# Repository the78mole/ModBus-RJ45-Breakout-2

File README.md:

# Modbus-RJ45-Breakout
A breakout board for Dual-ModBus-over-Twisted-Pair (RJ45) with isolated converters option

Here are some images of the first prototype, assembled with isolating RS485 transceivers. Echo already works, real testing on a ModBus will take place soon.

## Production Files

This repository includes an automated workflow that generates production-ready files for PCB manufacturing and assembly. The workflow creates:

- **Gerber Files** - Ready for PCB manufacturer submission
- **Drill Files** - For via and hole drilling
- **Schematic PDF** - Complete circuit documentation
- **Interactive BOM** - HTML component placement guide
- **3D STEP Model** - For mechanical design verification
- **PCB Renders** - Professional visualizations and assembly drawings

### Using the Production Workflow

The workflow automatically runs on:
- Every push to `main` branch
- Every pull request
- Manual trigger via "Actions" tab

**For Pull Requests:** Download artifacts directly from the workflow run to review changes.

**For Releases:** Production files are automatically attached to GitHub releases with semantic versioning.

### Manual Generation

To generate production files locally, ensure you have the required tools installed and run:

```bash
.github/scripts/generate-production-files.sh
```

Files will be generated in the `production/` directory.

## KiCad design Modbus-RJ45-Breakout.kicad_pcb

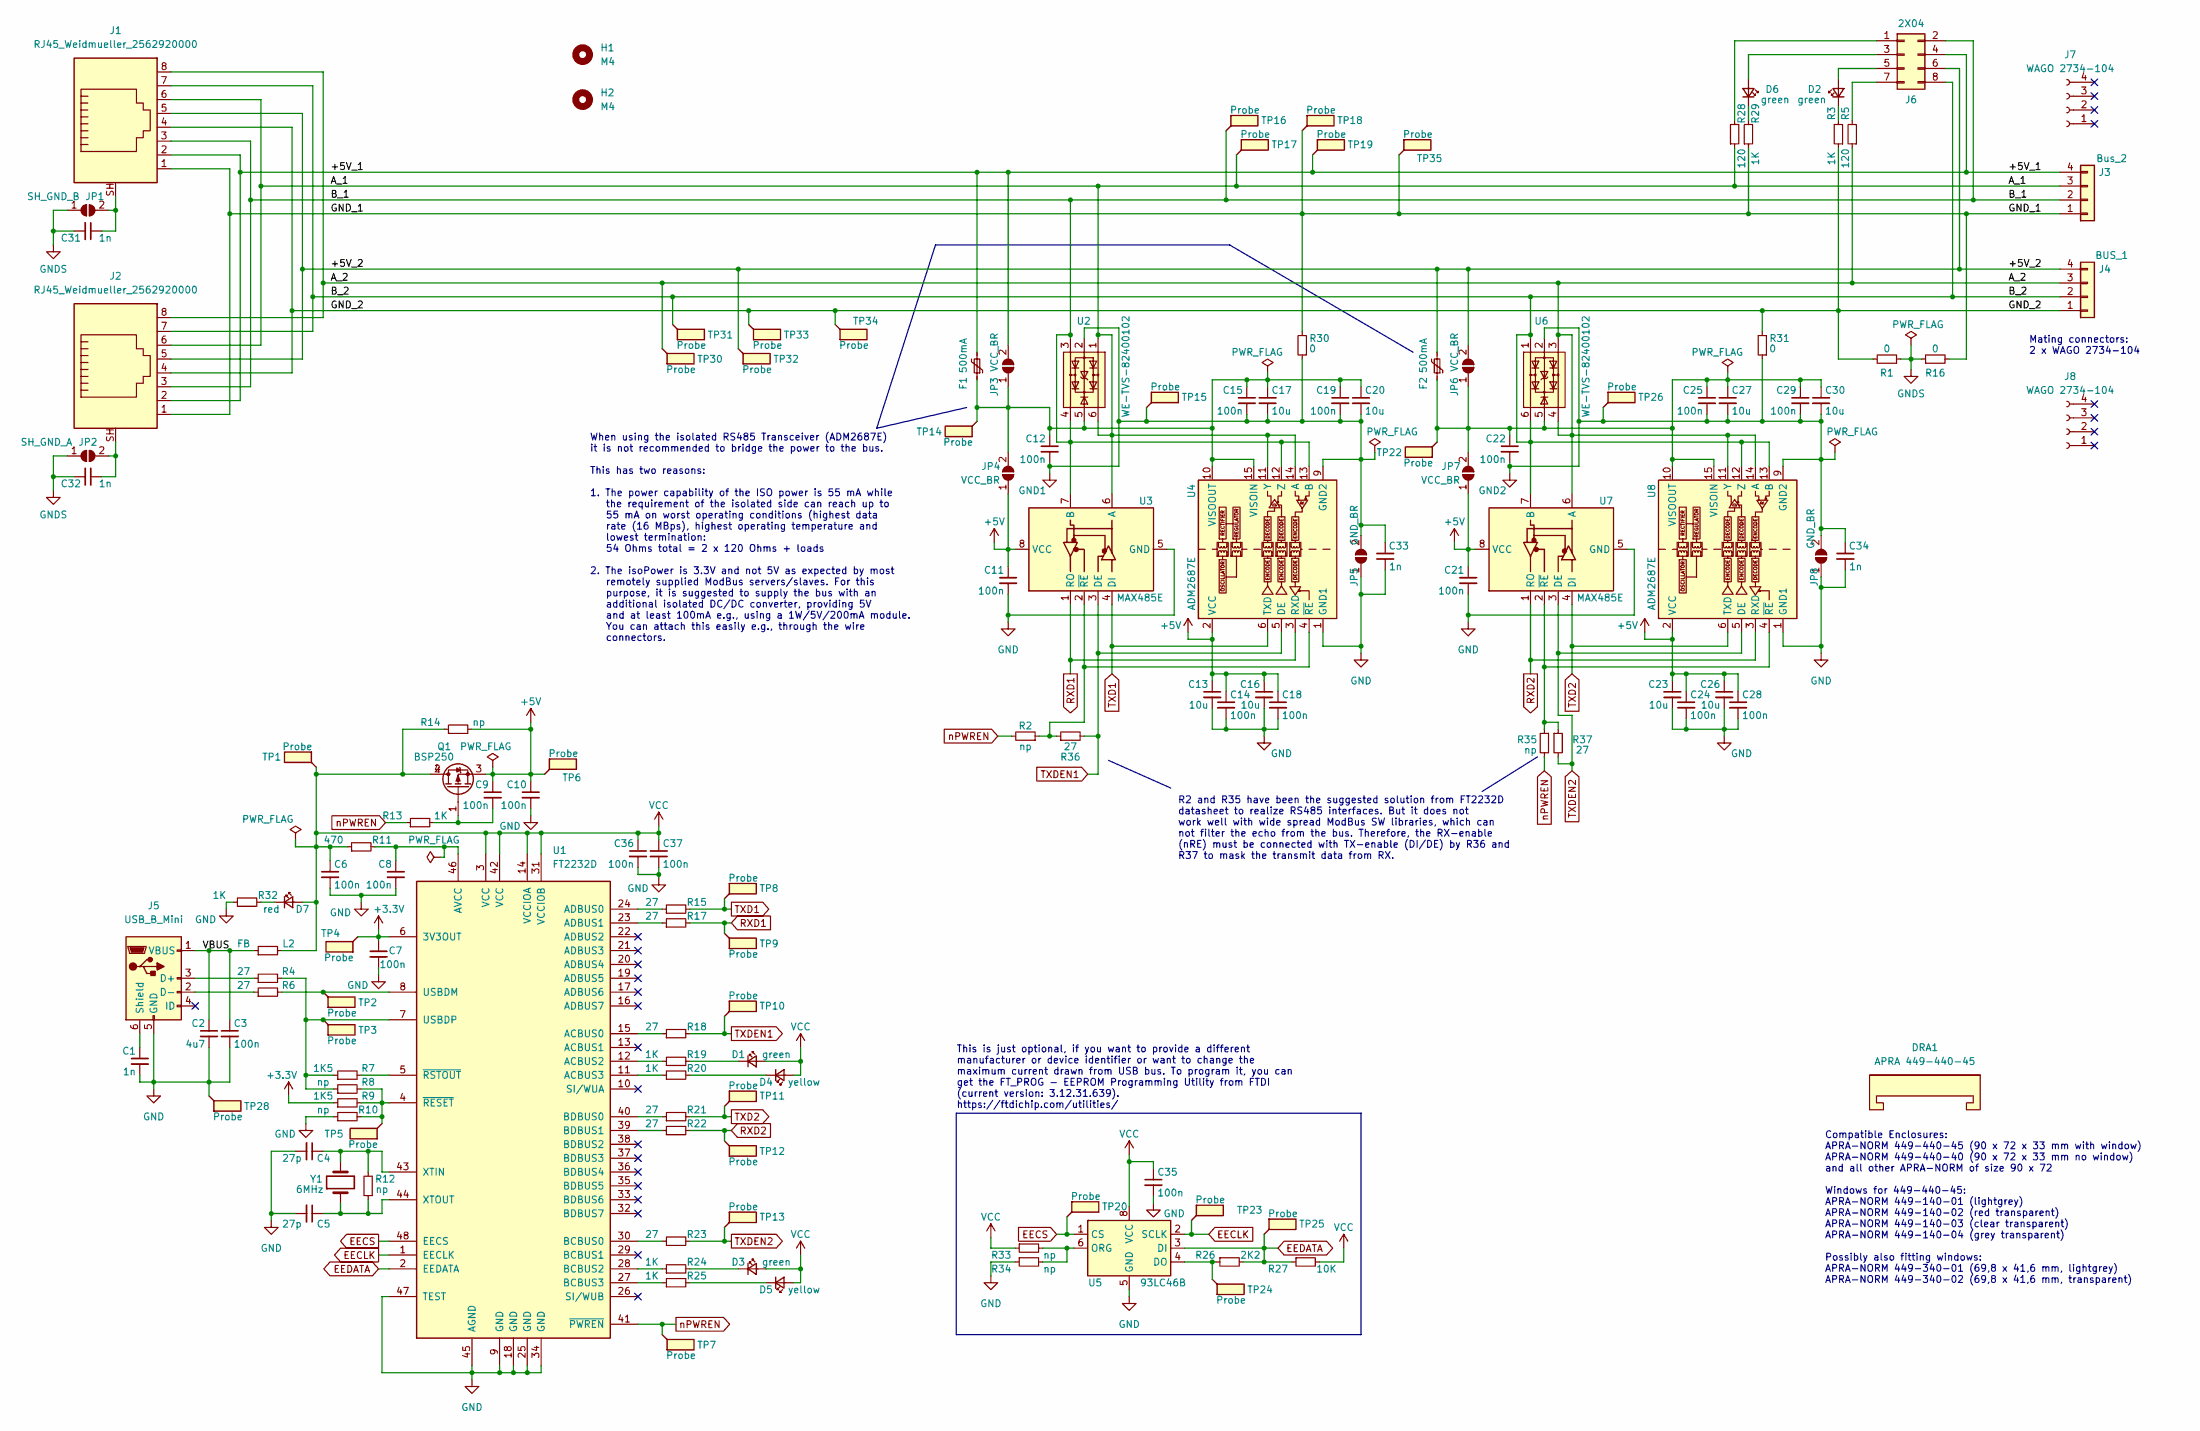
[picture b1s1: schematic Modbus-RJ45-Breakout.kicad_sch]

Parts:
C1, C31, C32, C33, C34: 1n; C_1206_3216Metric_Pad1.33x1.80mm_HandSolder
C2: 4u7; C_1206_3216Metric_Pad1.33x1.80mm_HandSolder
C3, C6, C7, C8, C9, C10, C11, C12, C14, C15, C18, C19, C21, C22, C24, C25, C28, C29, C35, C36, C37: 100n; C_0603_1608Metric_Pad1.08x0.95mm_HandSolder
C4, C5: 27p; C_0603_1608Metric_Pad1.08x0.95mm_HandSolder
C13, C16, C17, C20, C23, C26, C27, C30: 10u; C_1206_3216Metric_Pad1.33x1.80mm_HandSolder
D1, D2, D3, D6: green; LED_0603_1608Metric_Pad1.05x0.95mm_HandSolder
D4, D5: yellow; LED_0603_1608Metric_Pad1.05x0.95mm_HandSolder
D7: red; LED_0603_1608Metric_Pad1.05x0.95mm_HandSolder
DRA1: APRA 449-440-45; Dummy_0; MPN 449-440-45
F1, F2: 500mA; Fuse_1206_3216Metric_Pad1.42x1.75mm_HandSolder
H1, H2: M4; MountingHole_4.3mm_M4_DIN965
J1, J2: RJ45_Weidmueller_2562920000; RJ45_Weidmüller_2562920000_Horizontal
J3: Bus_2; Wago_734-164_1x04_P3.50mm_Horizontal
J4: BUS_1; Wago_734-164_1x04_P3.50mm_Horizontal
J5: USB_B_Mini; USB_Mini-B_Wuerth_65100516121_Horizontal
J6: 2X04; PinHeader_2x04_P2.54mm_Vertical_SMD
J7, J8: WAGO 2734-104; Dummy_0; MPN 2734-104
JP1: SH_GND_B; SolderJumper-2_P1.3mm_Open_TrianglePad1.0x1.5mm
JP2: SH_GND_A; SolderJumper-2_P1.3mm_Open_TrianglePad1.0x1.5mm
JP3, JP4, JP6, JP7: VCC_BR; SolderJumper-2_P1.3mm_Open_TrianglePad1.0x1.5mm
JP5, JP8: GND_BR; SolderJumper-2_P1.3mm_Open_TrianglePad1.0x1.5mm
L2: FB; R_0603_1608Metric_Pad0.98x0.95mm_HandSolder
Q1: BSP250; SOT-223
R1, R16: 0; R_1206_3216Metric_Pad1.30x1.75mm_HandSolder
R2, R8, R10, R12, R14, R33, R34, R35: np; R_0603_1608Metric_Pad0.98x0.95mm_HandSolder
R3, R13, R19, R20, R24, R25, R29, R32: 1K; R_0603_1608Metric_Pad0.98x0.95mm_HandSolder
R4, R6, R15, R17, R18, R21, R22, R23, R36, R37: 27; R_0603_1608Metric_Pad0.98x0.95mm_HandSolder
R5, R28: 120; R_0603_1608Metric_Pad0.98x0.95mm_HandSolder
R7, R9: 1K5; R_0603_1608Metric_Pad0.98x0.95mm_HandSolder
R11: 470; R_0603_1608Metric_Pad0.98x0.95mm_HandSolder
R26: 2K2; R_0603_1608Metric_Pad0.98x0.95mm_HandSolder
R27: 10K; R_0603_1608Metric_Pad0.98x0.95mm_HandSolder
R30, R31: 0; R_0603_1608Metric_Pad0.98x0.95mm_HandSolder
TP1, TP6, TP28, TP34, TP35: Probe; TestPoint_THTPad_2.0x2.0mm_Drill1.0mm
TP2, TP3, TP4, TP5, TP7, TP8, TP9, TP10, TP11, TP12, TP13, TP14, TP15, TP16, TP17, TP18, TP19, TP20, TP22, TP23, TP24, TP25, TP26, TP30, TP31, TP32, TP33: Probe; TestPoint_Pad_D1.5mm
U1: FT2232D; LQFP-48_7x7mm_P0.5mm
U2, U6: WE-TVS-82400102; SOT-23-6
U3, U7: MAX485E; SO-8_3.9x4.9mm_P1.27mm
U4, U8: ADM2687E; SOIC-16W_7.5x12.8mm_P1.27mm
U5: 93LC46B; SOIC-8_3.9x4.9mm_P1.27mm
Y1: 6MHz; Crystal_SMD_HC49-SD_HandSoldering

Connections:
+3V3: C7.1, R9.1, TP4.1, U1.6 (3V3OUT)
+5V: C9.1, C10.1, C11.1, C13.1, C14.1, C16.1, C18.1, C21.1, C23.1, C24.1, C26.1, C28.1, JP4.1 (A), JP7.1 (A), Q1.3 (S), R14.2, TP6.1, U3.8 (VCC), U4.2 (VCC), U4.7 (VCC), U7.8 (VCC), U8.2 (VCC), U8.7 (VCC)
/+5V_1: F1.2, J1.2, J2.2, J3.4, J6.4, JP3.2 (B), TP19.1
/+5V_2: F2.2, J1.5, J2.5, J4.4, J6.6, JP6.2 (B), TP32.1
/A_1: J1.6, J2.6, J3.3, R28.1, TP17.1, U2.1, U2.6, U3.6 (A), U4.11 (Y), U4.14 (A)
/A_2: J1.8, J2.8, J4.3, R5.1, TP30.1, U6.3, U6.4, U7.6 (A), U8.11 (Y), U8.14 (A)
/B_1: J1.3, J2.3, J3.2, J6.2, TP16.1, U2.3, U2.4, U3.7 (B), U4.12 (Z), U4.13 (B)
/B_2: J1.7, J2.7, J4.2, J6.8, TP31.1, U6.1, U6.6, U7.7 (B), U8.12 (Z), U8.13 (B)
/GND_1: J1.1, J2.1, J3.1, R16.2, R29.1, R30.2, TP18.1, TP35.1
/GND_2: J1.4, J2.4, J4.1, R1.2, R3.1, R31.2, TP33.1, TP34.1
/VBUS: C2.1, C3.1, J5.1 (VBUS), L2.1
EECLK: TP23.1, U1.1 (EECLK), U5.2 (SCLK)
EECS: TP20.1, U1.48 (EECS), U5.1 (CS)
EEDATA: R26.2, R27.1, TP25.1, U1.2 (EEDATA), U5.3 (DI)
GND: C1.2, C2.2, C3.2, C4.2, C5.2, C6.2, C7.2, C8.2, C10.2, C11.2, C13.2, C14.2, C16.2, C18.2, C21.2, C23.2, C24.2, C26.2, C28.2, C33.2, C34.2, C35.2, C36.2, C37.2, J5.5 (GND), JP5.1 (A), JP8.1 (A), R10.1, R32.1, R34.1, TP28.1, U1.9 (GND), U1.18 (GND), U1.25 (GND), U1.34 (GND), U1.45 (AGND), U1.47 (TEST), U3.5 (GND), U4.1 (GND1), U4.8 (GND1), U5.5 (GND), U7.5 (GND), U8.1 (GND1), U8.8 (GND1)
GND1: C12.2, C15.2, C17.2, C19.2, C20.2, C33.1, JP5.2 (B), R30.1, TP15.1, U2.2, U4.9 (GND2), U4.16 (GND2)
GND2: C22.2, C25.2, C27.2, C29.2, C30.2, C34.1, JP8.2 (B), R31.1, TP26.1, U6.2, U8.9 (GND2), U8.16 (GND2)
GNDS: C31.2, C32.2, JP1.1 (A), JP2.1 (A), R1.1, R16.1
unnamed: C1.1, J5.6 (Shield)
unnamed: C4.1, R12.2, U1.43 (XTIN), Y1.2
unnamed: C5.1, R12.1, U1.44 (XTOUT), Y1.1
unnamed: C8.1, R11.2, U1.46 (AVCC)
unnamed: C9.2, Q1.1 (D), R13.2
unnamed: C12.1, C15.1, C17.1, C19.1, C20.1, F1.1, JP3.1 (A), JP4.2 (B), TP14.1, U2.5, U4.10 (VISOOUT), U4.15 (VISOIN)
unnamed: C22.1, C25.1, C27.1, C29.1, C30.1, F2.1, JP6.1 (A), JP7.2 (B), TP22.1, U6.5, U8.10 (VISOOUT), U8.15 (VISOIN)
unnamed: C31.1, J1.SH, JP1.2 (B)
unnamed: C32.1, J2.SH, JP2.2 (B)
unnamed: D1.1 (K), R19.2
unnamed: D2.1 (K), R3.2
unnamed: D2.2 (A), J6.5
unnamed: D3.1 (K), R24.2
unnamed: D4.1 (K), R20.2
unnamed: D5.1 (K), R25.2
unnamed: D6.1 (K), R29.2
unnamed: D6.2 (A), J6.3
unnamed: D7.1 (K), R32.2
unnamed: J5.2 (D-), R6.1
unnamed: J5.3 (D+), R4.1
unnamed: J6.1, R28.2
unnamed: J6.7, R5.2
unnamed: R2.1, R36.1, U3.2 (~RE), U4.4 (~RE)
unnamed: R4.2, R7.1, R8.1, TP3.1, U1.7 (USBDP)
unnamed: R6.2, TP2.1, U1.8 (USBDM)
unnamed: R7.2, U1.5 (~RSTOUT)
unnamed: R8.2, R9.2, R10.2, TP5.1, U1.4 (~RESET)
unnamed: R15.1, U1.24 (ADBUS0)
unnamed: R17.1, U1.23 (ADBUS1)
unnamed: R18.1, U1.15 (ACBUS0)
unnamed: R19.1, U1.12 (ACBUS2)
unnamed: R20.1, U1.11 (ACBUS3)
unnamed: R21.1, U1.40 (BDBUS0)
unnamed: R22.1, U1.39 (BDBUS1)
unnamed: R23.1, U1.30 (BCBUS0)
unnamed: R24.1, U1.28 (BCBUS2)
unnamed: R25.1, U1.27 (BCBUS3)
unnamed: R26.1, TP24.1, U5.4 (DO)
unnamed: R33.2, R34.2, U5.6 (ORG)
unnamed: R35.1, R37.1, U7.2 (~RE), U8.4 (~RE)
RXD1: R17.2, TP9.1, U3.1 (RO), U4.3 (RXD)
RXD2: R22.2, TP12.1, U7.1 (RO), U8.3 (RXD)
TXD1: R15.2, TP8.1, U3.4 (DI), U4.6 (TXD)
TXD2: R21.2, TP11.1, U7.4 (DI), U8.6 (TXD)
TXDEN1: R18.2, R36.2, TP10.1, U3.3 (DE), U4.5 (DE)
TXDEN2: R23.2, R37.2, TP13.1, U7.3 (DE), U8.5 (DE)
VCC: C6.1, C35.1, C36.1, C37.1, D1.2 (A), D3.2 (A), D4.2 (A), D5.2 (A), D7.2 (A), L2.2, Q1.2 (G), Q1.4 (G), R11.1, R14.1, R27.2, R33.1, TP1.1, U1.3 (VCC), U1.14 (VCCIOA), U1.31 (VCCIOB), U1.42 (VCC), U5.8 (VCC)
nPWREN: R2.2, R13.1, R35.2, TP7.1, U1.41 (~PWREN)

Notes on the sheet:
Compatible Enclosures: APRA-NORM 449-440-45 (90 x 72 x 33 mm with window) APRA-NORM 449-440-40 (90 x 72 x 33 mm no window) and all other APRA-NORM of size 90 x 72 Windows for 449-440-45: APRA-NORM 449-140-01 (lightgrey) APRA-NORM 449-140-02 (red transparent) APRA-NORM 449-140-03 (clear transparent)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
When using the isolated RS485 Transceiver (ADM2687E) it is not recommended to bridge the power to the bus. This has two reasons: 1. The power capability of the ISO power is 55 mA while the requirement of the isolated side can reach up to 55 mA on worst operating conditions (highest data rate (16 MB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
Mating connectors: 2 x WAGO 2734-104
This is just optional, if you want to provide a different manufacturer or device identifier or want to change the maximum current drawn from USB bus. To program it, you can get the FT_PROG - EEPROM Programming Utility from FTDI (current version: 3.12.31.639). https://ftdichip.com/utilities/
R2 and R35 have been the suggested solution from FT2232D datasheet to realize RS485 interfaces. But it does not work well with wide spread ModBus SW libraries, which can not filter the echo from the bus. Therefore, the RX-enable (nRE) must be connected with TX-enable (DI/DE) by R36 and R37 to mask 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

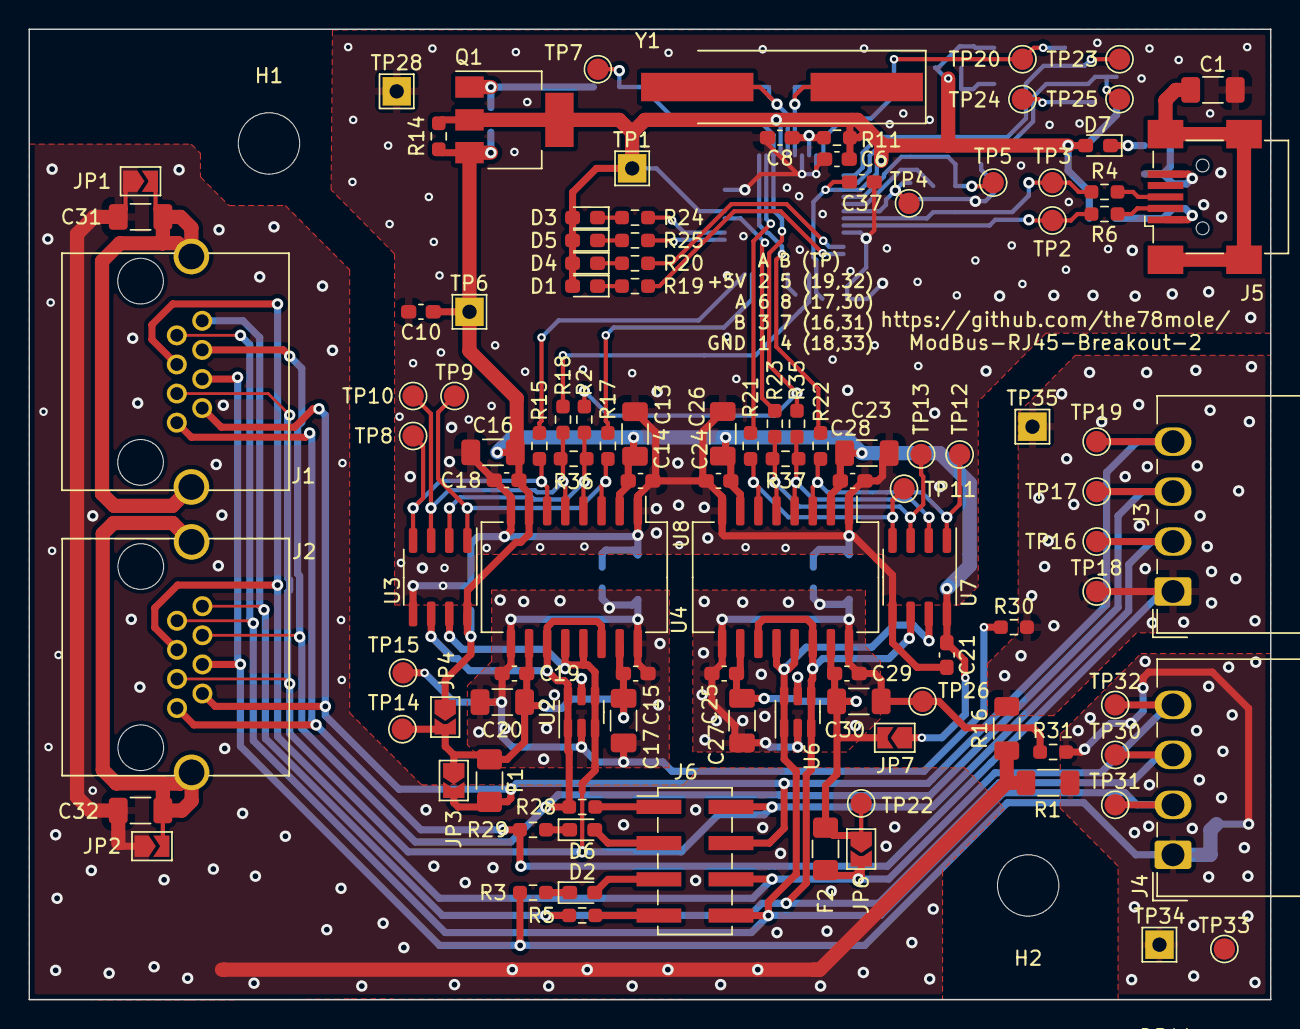
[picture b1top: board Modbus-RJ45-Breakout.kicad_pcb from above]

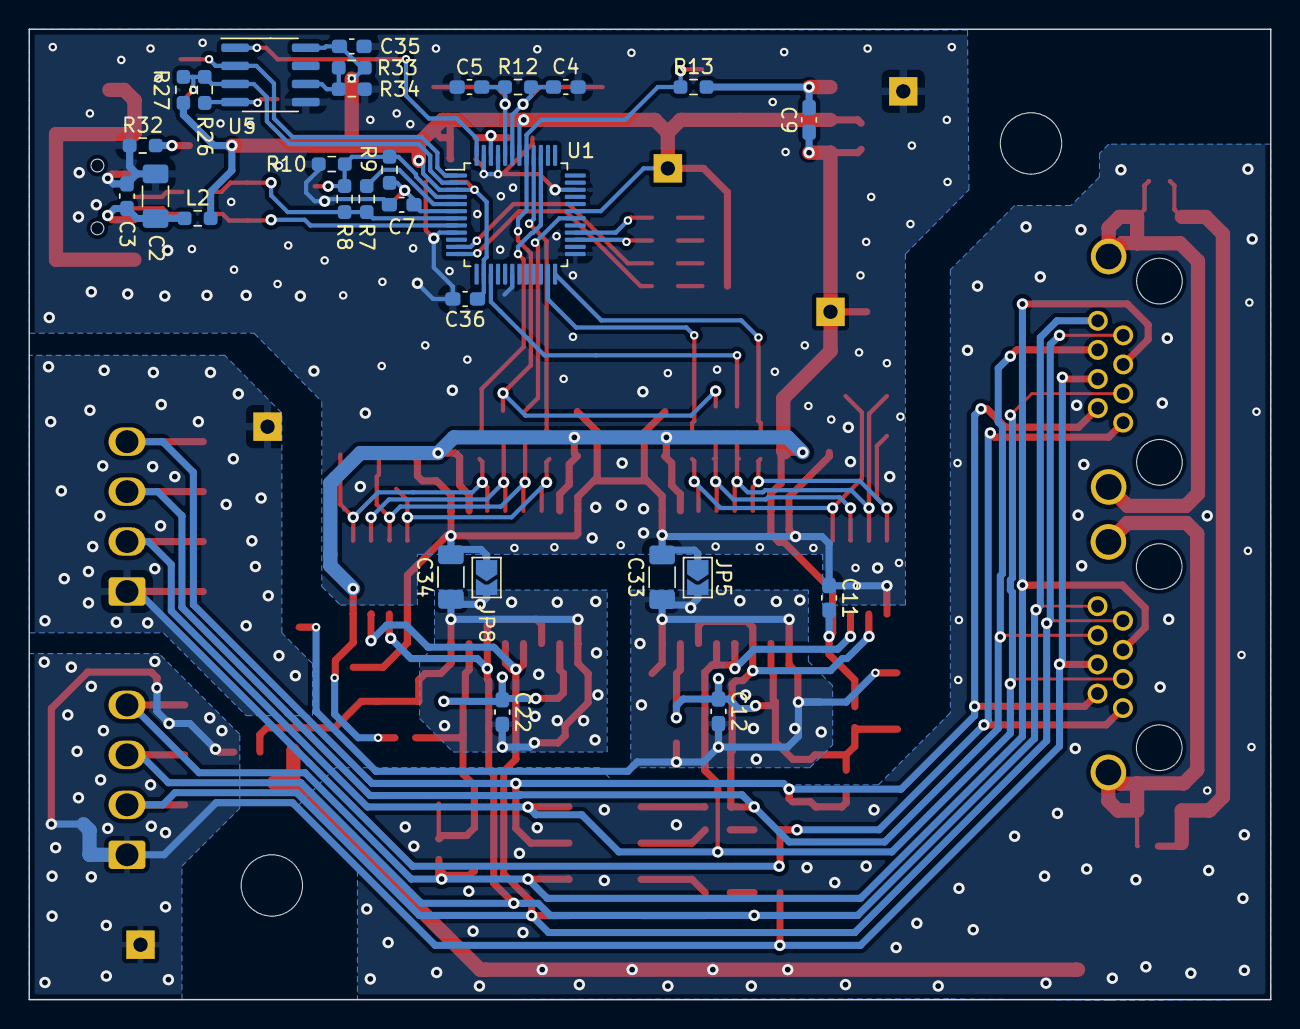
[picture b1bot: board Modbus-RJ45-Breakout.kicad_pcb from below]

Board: 2 copper layers, 87.0 x 68.0 mm, 145 parts (29 on the bottom side), 66 nets.

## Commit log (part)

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2023-05-07 Moved the USB-Power LED to a more central position
    Since many cases have their clear view window in the center,
    I moved the USB Power LED also there to be easily visible.
2023-05-07 Removed unused Schamtic sheets
    These have been the 2 USB converters in the older design
    and are not needed anymore. Everything is contained in
    the A3 main sheet.
2023-05-19 Partly improved and re-routed
2023-05-20 As ordered, added info on enclosures
2023-05-30 Fixed TP docs on PCB and added ibom
2023-06-01 Adjustments during prototype build
2023-06-01 Added some prototype images
2023-06-01 Moved the terminal docs to the middle of the PCB
    ...to be able to read it through the cut out of the case.
2023-06-01 RS485 bus echo solved and A<->B swap with ISO Transceivers (schematic only)
    This can be solved also with the current PCB by swapping the A and B externally
    and not mixing ISO and non-ISO bus transceivers. The RX-Enable problem can be solved
    by a desoldering R2 and R35 and bridging the pads to R18 and R23 resp. close to the transceiver.
2023-06-02 Fixed all issues and added Gerber exports
2023-06-02 Version bump 1.0.0
2023-06-02 Added an image of a fixed 0.0.2 board
2025-09-12 Initial plan
2025-09-12 feat: add KiCad production files workflow and scripts
2025-09-12 docs: add production workflow documentation and update gitignore
2025-09-12 Add Renovate configuration file
2025-09-12 Fix release artifact naming mismatch: use correct KiCad project filenames
2025-09-12 Improve release artifact handling: add manufacturing package download and use robust file search
